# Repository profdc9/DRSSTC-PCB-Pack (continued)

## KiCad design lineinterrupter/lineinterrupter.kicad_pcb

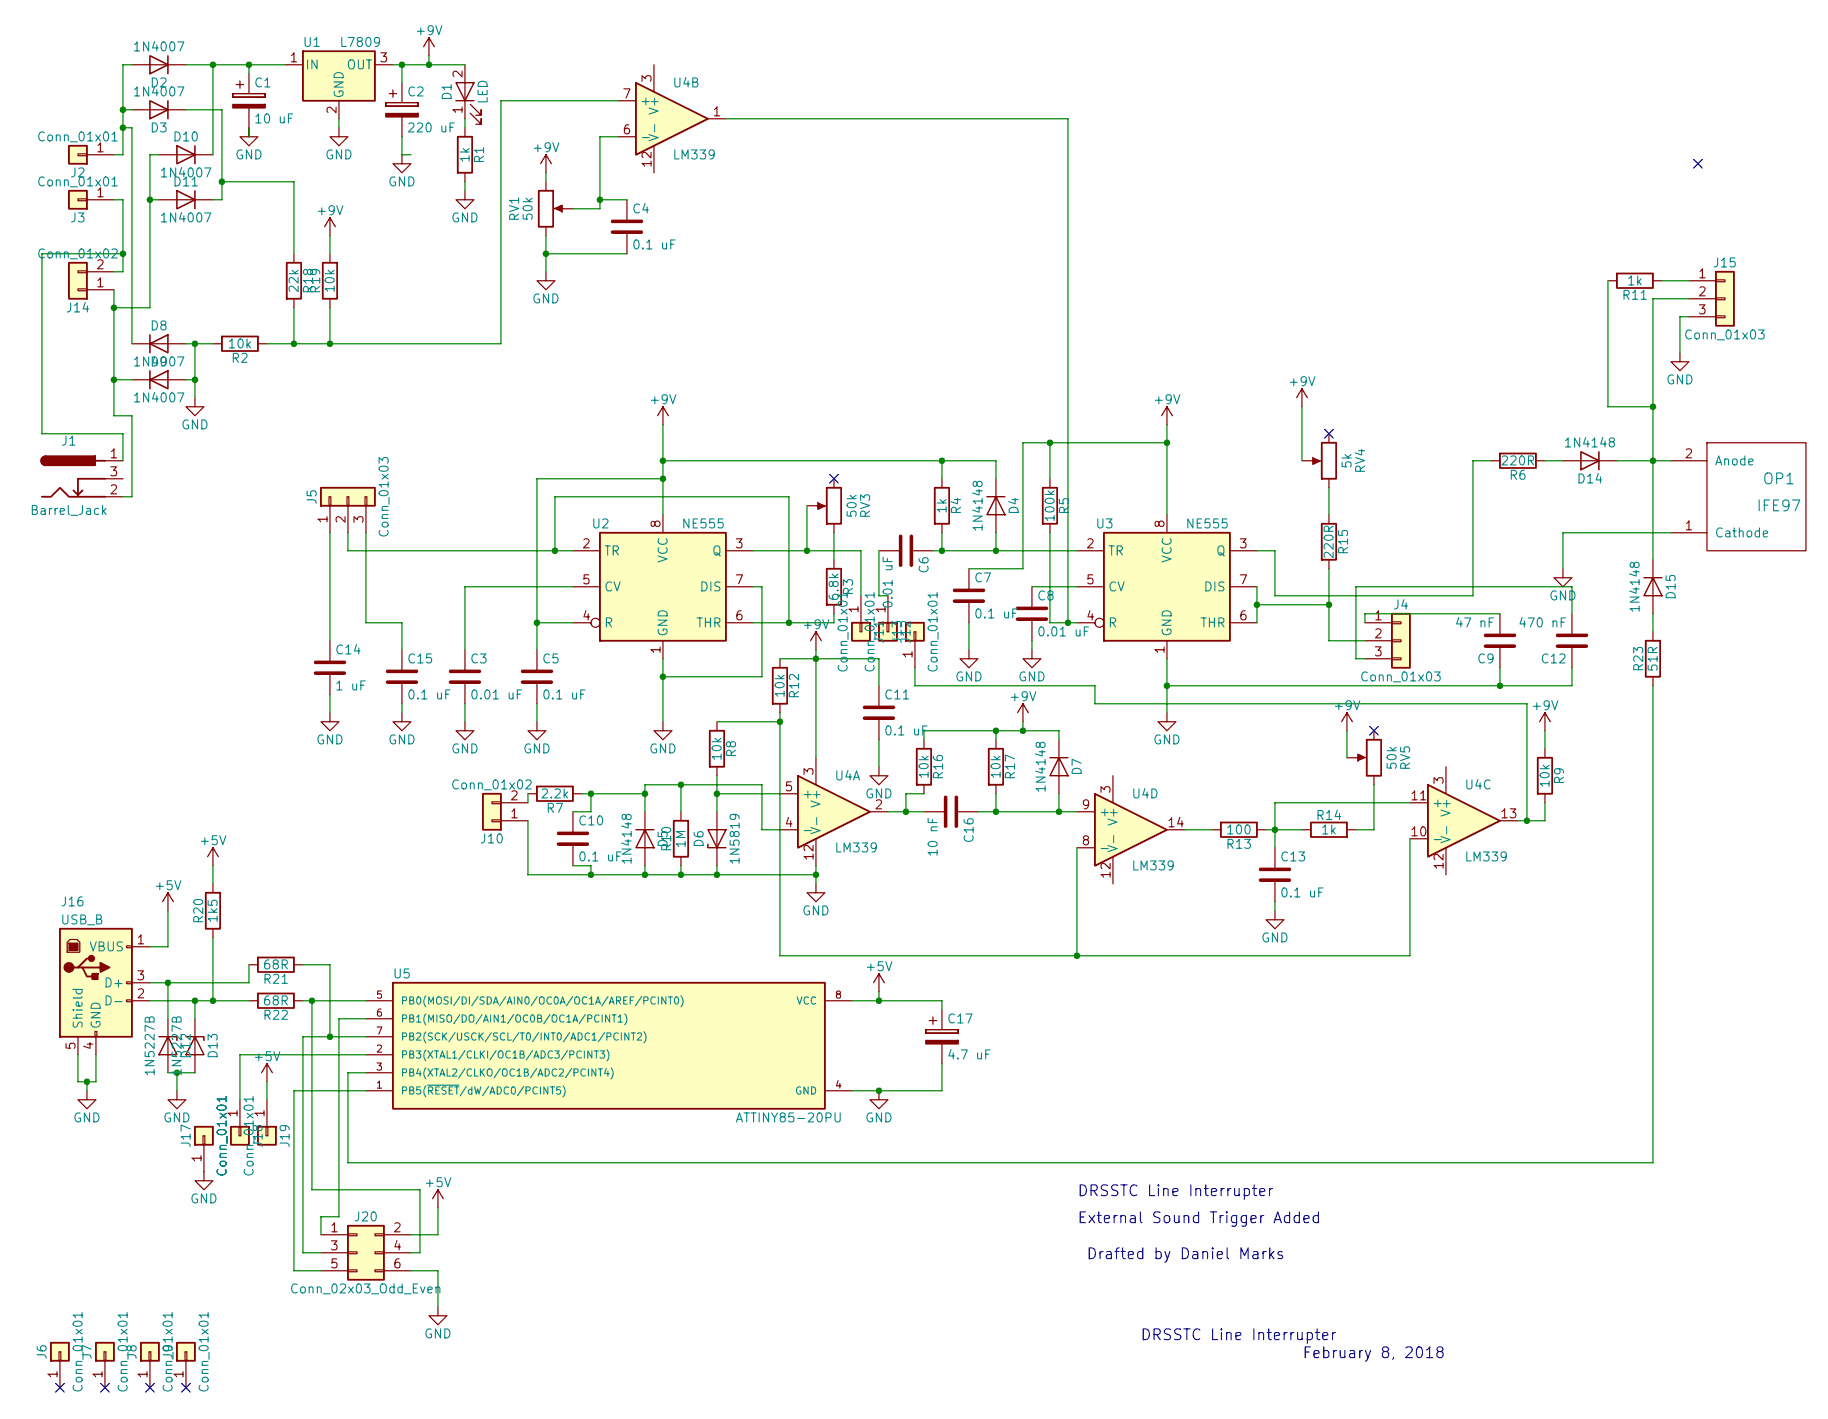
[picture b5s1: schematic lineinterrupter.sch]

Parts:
C1: 10 uF; CP_Radial_D6.3mm_P2.50mm
C2: 220 uF; CP_Radial_D6.3mm_P2.50mm
C3, C6, C8: 0.01 uF; C_Disc_D7.5mm_W4.4mm_P5.00mm
C4, C5, C7, C10, C11, C13, C15: 0.1 uF; C_Disc_D7.5mm_W4.4mm_P5.00mm
C9: 47 nF; C_Disc_D7.5mm_W4.4mm_P5.00mm
C12: 470 nF; C_Disc_D7.5mm_W4.4mm_P5.00mm
C14: 1 uF; C_Disc_D7.5mm_W4.4mm_P5.00mm
C16: 10 nF; C_Disc_D7.5mm_W4.4mm_P5.00mm
C17: 4.7 uF; CP_Radial_D6.3mm_P2.50mm
D1: LED; LED_D5.0mm
D2, D3, D8, D9, D10, D11: 1N4007; D_DO-41_SOD81_P10.16mm_Horizontal
D4, D5, D7, D14, D15: 1N4148; D_DO-41_SOD81_P7.62mm_Horizontal
D6: 1N5819; D_DO-41_SOD81_P7.62mm_Horizontal
D12, D13: 1N5227B; D_DO-41_SOD81_P10.16mm_Horizontal
J1: Barrel_Jack; BARREL_JACK
J2, J3, J6, J7, J8, J9, J11, J12, J13, J17, J18, J19: Conn_01x01; 1pin
J4, J5: Conn_01x03; Pin_Header_Straight_1x03_Pitch2.54mm
J10, J14: Conn_01x02; TerminalBlock_bornier-2_P5.08mm
J15: Conn_01x03; TerminalBlock_bornier-3_P5.08mm
J16: USB_B
J20: Conn_02x03_Odd_Even; Pin_Header_Straight_2x03_Pitch2.54mm
OP1: IFE97
R1, R4, R11, R14: 1k; R_Axial_DIN0309_L9.0mm_D3.2mm_P12.70mm_Horizontal
R2, R8, R9, R12, R16, R17, R19: 10k; R_Axial_DIN0309_L9.0mm_D3.2mm_P12.70mm_Horizontal
R3: 6.8k; R_Axial_DIN0309_L9.0mm_D3.2mm_P12.70mm_Horizontal
R5: 100k; R_Axial_DIN0309_L9.0mm_D3.2mm_P12.70mm_Horizontal
R6, R15: 220R; R_Axial_DIN0309_L9.0mm_D3.2mm_P12.70mm_Horizontal
R7: 2.2k; R_Axial_DIN0309_L9.0mm_D3.2mm_P12.70mm_Horizontal
R10: 1M; R_Axial_DIN0309_L9.0mm_D3.2mm_P12.70mm_Horizontal
R13: 100; R_Axial_DIN0309_L9.0mm_D3.2mm_P12.70mm_Horizontal
R18: 22k; R_Axial_DIN0309_L9.0mm_D3.2mm_P12.70mm_Horizontal
R20: 1k5; R_Axial_DIN0309_L9.0mm_D3.2mm_P12.70mm_Horizontal
R21, R22: 68R; R_Axial_DIN0309_L9.0mm_D3.2mm_P12.70mm_Horizontal
R23: 51R; R_Axial_DIN0309_L9.0mm_D3.2mm_P12.70mm_Horizontal
RV1, RV3, RV5: 50k; Potentiometer_WirePads
RV4: 5k; Potentiometer_WirePads
U1: L7809; TO-220-3_Vertical
U2, U3: NE555; DIP-8_W7.62mm_Socket
U4: LM339; DIP-14_W7.62mm_Socket
U5: ATTINY85-20PU; DIP-8_W7.62mm_Socket

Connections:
+5V: C17.1, J16.1 (VBUS), J19.1, J20.2, R20.2, U5.8 (VCC)
+9V: C2.1, C5.1, C7.1, C11.1, D1.2 (A), D4.1 (K), D7.1 (K), R4.1, R5.1, R9.1, R12.1, R16.1, R17.1, R19.2, RV1.1, RV4.2, RV5.2, U1.3 (OUT), U2.4 (R), U2.8 (VCC), U3.8 (VCC), U4.3 (V+)
GND: C1.2, C2.2, C3.2, C4.2, C5.2, C7.2, C8.2, C9.1, C10.2, C11.2, C12.1, C13.2, C14.2, C15.2, C17.2, D5.2 (A), D6.1 (K), D8.2 (A), D9.2 (A), D12.2 (A), D13.2 (A), J10.1, J15.3, J16.4 (GND), J16.5 (Shield), J17.1, J20.6, OP1.1 (Cathode), R1.2, R2.2, R10.1, RV1.3, U1.2 (GND), U2.1 (GND), U2.7 (DIS), U3.1 (GND), U4.12 (V-), U5.4 (GND)
unnamed: C1.1, D2.1 (K), D10.1 (K), U1.1 (IN)
unnamed: C3.1, U2.5 (CV)
unnamed: C4.1, RV1.2, U4.6 (-)
unnamed: C6.1, D4.2 (A), R4.2, U3.2 (TR)
unnamed: C6.2, J12.1
unnamed: C8.1, U3.5 (CV)
unnamed: C9.2, J4.1
unnamed: C10.1, D5.1 (K), R7.1, R10.2, U4.4 (-)
unnamed: C12.2, J4.3
unnamed: C13.1, R13.1, R14.1, U4.11 (+)
unnamed: C14.1, J5.1
unnamed: C15.1, J5.3
unnamed: C16.1, D7.2 (A), R17.2, U4.9 (+)
unnamed: C16.2, R16.2, U4.2
unnamed: D1.1 (K), R1.1
unnamed: D2.2 (A), D3.2 (A), D8.1 (K), J2.1
unnamed: D6.2 (A), R8.2, U4.5 (+)
unnamed: D9.1 (K), D10.2 (A), D11.2 (A), J1.2, J14.1
unnamed: D3.1 (K), D11.1 (K), R18.1
unnamed: D12.1 (K), J16.3 (D+), R21.2
unnamed: D13.1 (K), J16.2 (D-), R20.1, R22.2
unnamed: D14.1 (K), D15.1 (K), J15.2, OP1.2 (Anode), R11.2
unnamed: D14.2 (A), R6.1
unnamed: D15.2 (A), R23.2
unnamed: J1.1, J3.1, J14.2
unnamed: J4.2, R15.2, U3.6 (THR), U3.7 (DIS)
unnamed: J5.2, R3.2, U2.2 (TR), U2.6 (THR)
unnamed: J10.2, R7.2
unnamed: J11.1, RV3.2, U2.3 (Q)
unnamed: J13.1, R9.2, U4.13
unnamed: J15.1, R11.1
unnamed: J18.1, U5.2 (PB3(XTAL1/CLKI/OC1B/ADC3/PCINT3))
unnamed: J20.1, U5.6 (PB1(MISO/DO/AIN1/OC0B/OC1A/PCINT1))
unnamed: J20.3, R21.1, U5.7 (PB2(SCK/USCK/SCL/T0/INT0/ADC1/PCINT2))
unnamed: J20.4, R22.1, U5.5 (PB0(MOSI/DI/SDA/AIN0/OC0A/OC1A/AREF/PCI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)
unnamed: J20.5, U5.1 (PB5(~RESET~/dW/ADC0/PCINT5))
unnamed: R3.1, RV3.1
unnamed: R5.2, U3.4 (R), U4.1
unnamed: R6.2, U3.3 (Q)
unnamed: R8.1, R12.2, U4.8 (-), U4.10 (-)
unnamed: R13.2, U4.14
unnamed: R14.2, RV5.3
unnamed: R15.1, RV4.1
unnamed: R2.1, R18.2, R19.1, U4.7 (+)
unnamed: R23.1, U5.3 (PB4(XTAL2/CLKO/OC1B/ADC2/PCINT4))

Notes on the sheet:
DRSSTC Line Interrupter
DRSSTC Line Interrupter
External Sound Trigger Added
February 8, 2018
Drafted by Daniel Marks

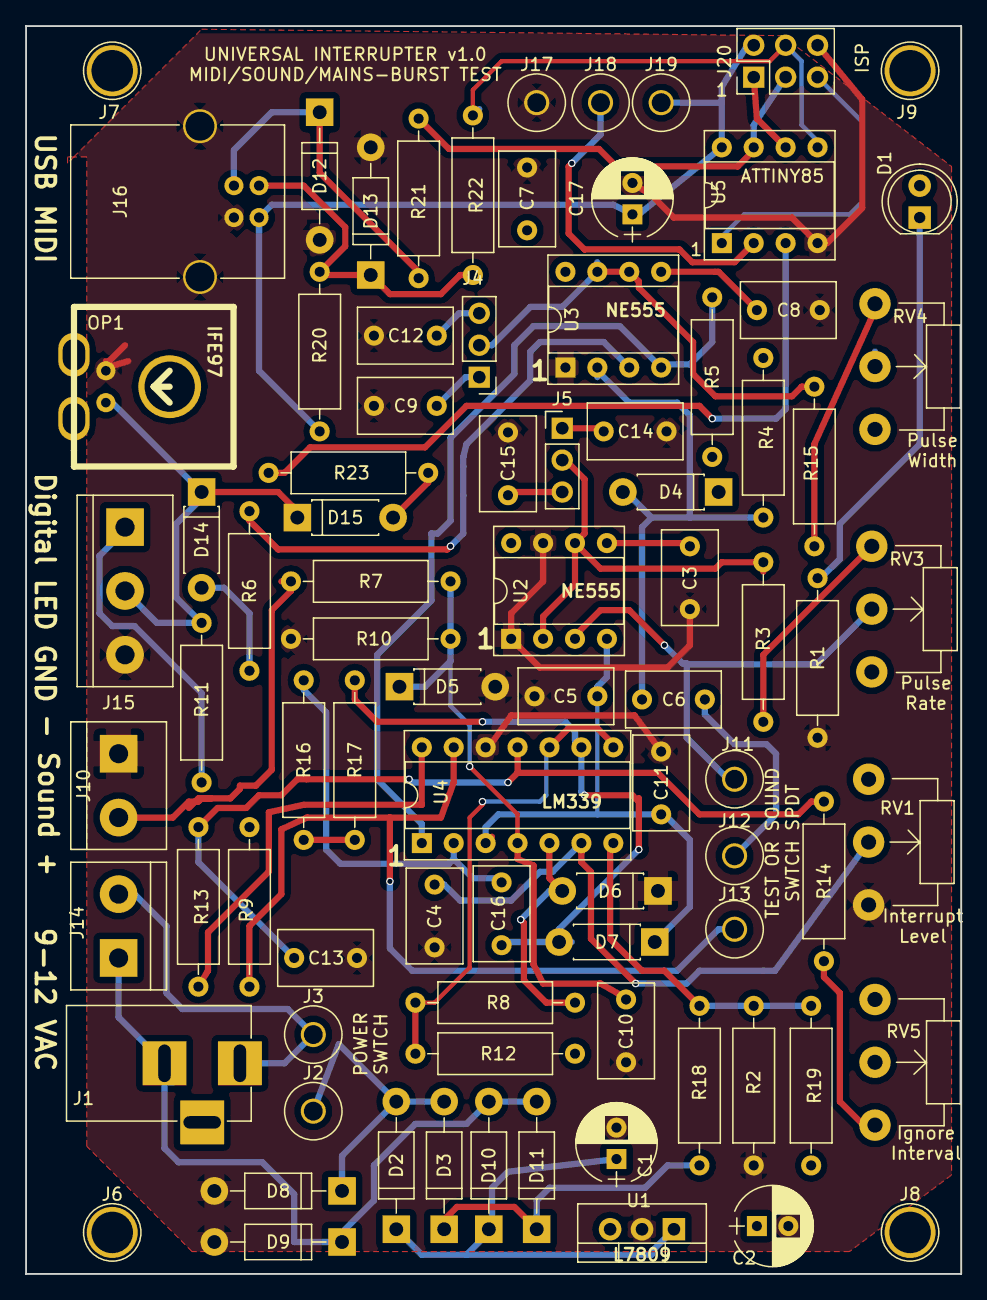
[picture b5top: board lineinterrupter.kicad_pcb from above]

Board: 2 copper layers, 74.4 x 99.3 mm, 85 parts (0 on the bottom side), 48 nets.

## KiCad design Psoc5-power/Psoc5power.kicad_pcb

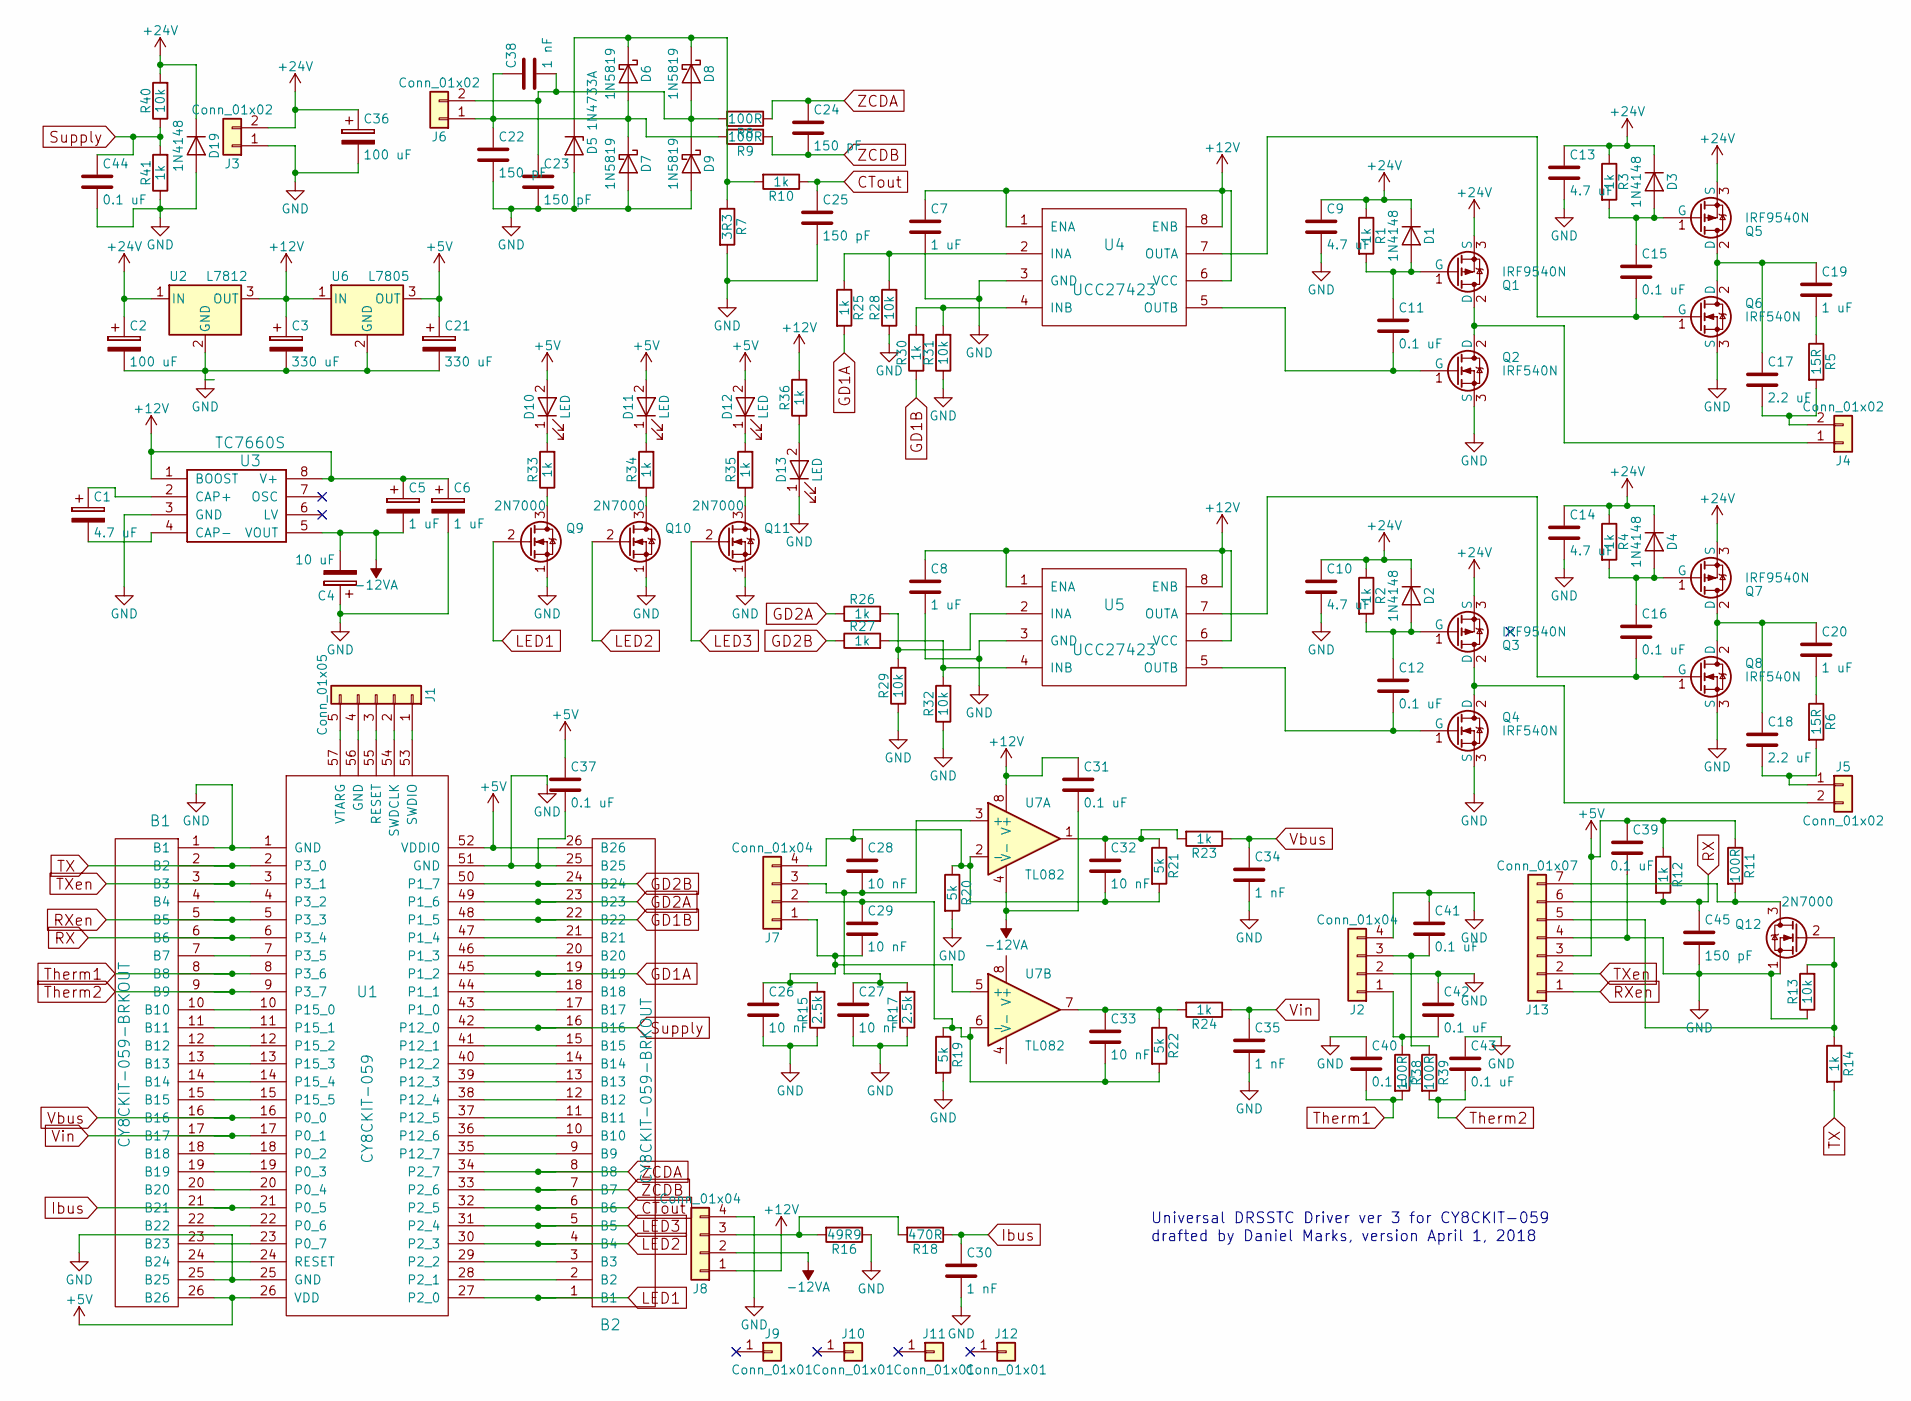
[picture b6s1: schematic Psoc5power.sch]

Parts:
B1, B2: CY8CKIT-059-BRKOUT
C1: 4.7 uF; CP_Radial_D6.3mm_P2.50mm
C2, C36: 100 uF; CP_Radial_D10.0mm_P5.00mm
C3, C21: 330 uF; CP_Radial_D10.0mm_P5.00mm
C4: 10 uF; CP_Radial_D6.3mm_P2.50mm
C5, C6: 1 uF; CP_Radial_D5.0mm_P2.50mm
C7, C8: 1 uF; C_Disc_D5.0mm_W2.5mm_P5.00mm
C9, C10, C13, C14: 4.7 uF; C_Disc_D7.5mm_W2.5mm_P5.00mm
C11, C12, C15, C16, C31, C37, C39, C40, C41, C42, C43, C44: 0.1 uF; C_Disc_D5.0mm_W2.5mm_P5.00mm
C17, C18: 2.2 uF; C_Disc_D7.5mm_W2.5mm_P5.00mm
C19, C20: 1 uF; C_Disc_D7.5mm_W2.5mm_P5.00mm
C22, C23, C24, C25, C45: 150 pF; C_Disc_D5.0mm_W2.5mm_P5.00mm
C26, C27, C32, C33: 10 nF; C_Disc_D5.0mm_W2.5mm_P5.00mm
C28, C29: 10 nF; C_Disc_D6.0mm_W2.5mm_P5.00mm
C30, C34, C35, C38: 1 nF; C_Disc_D5.0mm_W2.5mm_P5.00mm
D1, D2, D3, D4: 1N4148; D_DO-41_SOD81_P10.16mm_Horizontal
D5: 1N4733A; D_DO-41_SOD81_P10.16mm_Horizontal
D6, D7, D8, D9: 1N5819; D_DO-41_SOD81_P10.16mm_Horizontal
D10, D11, D12, D13: LED; LED_D3.0mm
D19: 1N4148; D_DO-35_SOD27_P7.62mm_Horizontal
J1: Conn_01x05; Pin_Header_Straight_1x05_Pitch2.54mm
J2, J7, J8: Conn_01x04; Molex_KK-6410-04_04x2.54mm_Straight
J3, J4, J5, J6: Conn_01x02; TerminalBlock_bornier-2_P5.08mm
J9, J10, J11, J12: Conn_01x01; 1pin
J13: Conn_01x07; Molex_KK-6410-07_07x2.54mm_Straight
Q1, Q3, Q5, Q7: IRF9540N; TO-220-3_Vertical
Q2, Q4, Q6, Q8: IRF540N; TO-220-3_Vertical
Q9, Q10, Q11, Q12: 2N7000; TO-92_Molded_Narrow
R1, R2, R3, R4, R10, R12, R14, R23, R24, R25, R26, R27, R30, R33, R34, R35, R36, R41: 1k; R_Axial_DIN0207_L6.3mm_D2.5mm_P7.62mm_Horizontal
R5, R6: 15R; R_Axial_DIN0414_L11.9mm_D4.5mm_P15.24mm_Horizontal
R7: 3R3; R_Axial_DIN0309_L9.0mm_D3.2mm_P12.70mm_Horizontal
R8, R9: 100R; R_Axial_DIN0309_L9.0mm_D3.2mm_P12.70mm_Horizontal
R11, R38, R39: 100R; R_Axial_DIN0207_L6.3mm_D2.5mm_P7.62mm_Horizontal
R13, R28, R29, R31, R32, R40: 10k; R_Axial_DIN0207_L6.3mm_D2.5mm_P7.62mm_Horizontal
R15, R17: 2.5k; R_Axial_DIN0207_L6.3mm_D2.5mm_P7.62mm_Horizontal
R16: 49R9; R_Axial_DIN0207_L6.3mm_D2.5mm_P7.62mm_Horizontal
R18: 470R; R_Axial_DIN0207_L6.3mm_D2.5mm_P7.62mm_Horizontal
R19, R20, R21, R22: 5k; R_Axial_DIN0207_L6.3mm_D2.5mm_P7.62mm_Horizontal
U1: CY8CKIT-059
U2: L7812; TO-220-3_Vertical
U3: TC7660S; DIP-8_W7.62mm_Socket
U4, U5: UCC27423; DIP-8_W7.62mm_Socket
U6: L7805; TO-220-3_Vertical
U7: TL082; DIP-8_W7.62mm_Socket

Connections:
+5V: B1.26 (B26), B2.26 (B26), C21.1, C37.1, C39.1, D10.2 (A), D11.2 (A), D12.2 (A), J13.3, R11.1, R12.1, U1.26 (VDD), U1.52 (VDDIO), U6.3 (OUT)
+24V: C2.1, C9.1, C10.1, C13.1, C14.1, C36.1, D1.1 (K), D2.1 (K), D3.1 (K), D4.1 (K), D19.1 (K), J3.2, Q1.3 (S), Q3.3 (S), Q5.3 (S), Q7.3 (S), R1.1, R2.1, R3.1, R4.1, R40.2, U2.1 (IN)
-12VA: C4.2, C5.2, C31.2, J8.2, U3.5 (VOUT), U7.4 (V-)
CTout: B2.6 (B6), C25.1, R10.1, U1.32 (P2_5)
GD1A: B2.19 (B19), R25.2, U1.45 (P1_2)
GD1B: B2.22 (B22), R30.1, U1.48 (P1_5)
GD2A: B2.23 (B23), R26.1, U1.49 (P1_6)
GD2B: B2.24 (B24), R27.1, U1.50 (P1_7)
GND: B1.1 (B1), B1.25 (B25), B2.25 (B25), C2.2, C3.2, C4.1, C6.2, C7.2, C8.2, C9.2, C10.2, C13.2, C14.2, C21.2, C22.2, C23.2, C25.2, C26.2, C27.2, C30.2, C34.2, C35.2, C36.2, C37.2, C39.2, C40.1, C41.1, C42.1, C43.1, C44.2, C45.2, D5.2 (A), D7.2 (A), D9.2 (A), D13.1 (K), D19.2 (A), J2.2, J2.4, J3.1, J8.4, J13.4, Q2.3 (S), Q4.3 (S), Q6.3 (S), Q8.3 (S), Q9.1 (S), Q10.1 (S), Q11.1 (S), Q12.1 (S), R7.2, R13.1, R15.1, R16.1, R17.1, R19.2, R20.2, R28.1, R29.1, R31.1, R32.1, R41.1, U1.1 (GND), U1.25 (GND), U1.51 (GND), U2.2 (GND), U3.3 (GND), U4.3 (GND), U5.3 (GND), U6.2 (GND)
Ibus: B1.21 (B21), C30.1, R18.1, U1.21 (P0_5)
LED1: B2.1 (B1), Q9.2 (G), U1.27 (P2_0)
LED2: B2.4 (B4), Q10.2 (G), U1.30 (P2_3)
LED3: B2.5 (B5), Q11.2 (G), U1.31 (P2_4)
unnamed: B1.4 (B4), U1.4 (P3_2)
unnamed: B1.7 (B7), U1.7 (P3_5)
unnamed: B1.10 (B10), U1.10 (P15_0)
unnamed: B1.11 (B11), U1.11 (P15_1)
unnamed: B1.12 (B12), U1.12 (P15_2)
unnamed: B1.13 (B13), U1.13 (P15_3)
unnamed: B1.14 (B14), U1.14 (P15_4)
unnamed: B1.15 (B15), U1.15 (P15_5)
unnamed: B1.18 (B18), U1.18 (P0_2)
unnamed: B1.19 (B19), U1.19 (P0_3)
unnamed: B1.20 (B20), U1.20 (P0_4)
unnamed: B1.22 (B22), U1.22 (P0_6)
unnamed: B1.23 (B23), U1.23 (P0_7)
unnamed: B1.24 (B24), U1.24 (RESET)
unnamed: B2.2 (B2), U1.28 (P2_1)
unnamed: B2.3 (B3), U1.29 (P2_2)
unnamed: B2.9 (B9), U1.35 (P12_7)
unnamed: B2.10 (B10), U1.36 (P12_6)
unnamed: B2.11 (B11), U1.37 (P12_5)
unnamed: B2.12 (B12), U1.38 (P12_4)
unnamed: B2.13 (B13), U1.39 (P12_3)
unnamed: B2.14 (B14), U1.40 (P12_2)
unnamed: B2.15 (B15), U1.41 (P12_1)
unnamed: B2.17 (B17), U1.43 (P1_0)
unnamed: B2.18 (B18), U1.44 (P1_1)
unnamed: B2.20 (B20), U1.46 (P1_3)
unnamed: B2.21 (B21), U1.47 (P1_4)
unnamed: C1.1, U3.2 (CAP+)
unnamed: C1.2, U3.4 (CAP-)
unnamed: C11.1, D1.2 (A), Q1.1 (G), R1.2
unnamed: C11.2, Q2.1 (G), U4.5 (OUTB)
unnamed: C12.1, D2.2 (A), Q3.1 (G), R2.2
unnamed: C12.2, Q4.1 (G), U5.5 (OUTB)
unnamed: C15.1, D3.2 (A), Q5.1 (G), R3.2
unnamed: C15.2, Q6.1 (G), U4.7 (OUTA)
unnamed: C16.1, D4.2 (A), Q7.1 (G), R4.2
unnamed: C16.2, Q8.1 (G), U5.7 (OUTA)
unnamed: C17.1, C19.1, Q5.2 (D), Q6.2 (D)
unnamed: C17.2, J4.2, R5.2
unnamed: C18.1, C20.1, Q7.2 (D), Q8.2 (D)
unnamed: C18.2, J5.1, R6.2
unnamed: C19.2, R5.1
unnamed: C20.2, R6.1
unnamed: C22.1, C38.1, D6.2 (A), D7.1 (K), J6.1, R9.2
unnamed: C23.1, C38.2, D8.2 (A), D9.1 (K), J6.2, R8.2
unnamed: C26.1, C29.2, J7.1, R15.2, U7.5 (+)
unnamed: C27.1, C28.2, J7.3, R17.2, U7.3 (+)
unnamed: C28.1, C32.2, J7.4, R20.1, R21.2, U7.2 (-)
unnamed: C29.1, C33.2, J7.2, R19.1, R22.2, U7.6 (-)
unnamed: C32.1, R21.1, R23.2, U7.1
unnamed: C33.1, R22.1, R24.2, U7.7
unnamed: C41.2, J2.3, R39.1
unnamed: C42.2, J2.1, R38.1
unnamed: D5.1 (K), D6.1 (K), D8.1 (K), R7.1, R10.2
unnamed: D10.1 (K), R33.2
unnamed: D11.1 (K), R34.2
unnamed: D12.1 (K), R35.2
unnamed: D13.2 (A), R36.1
unnamed: J1.1, U1.53 (SWDIO)
unnamed: J1.2, U1.54 (SWDCLK)
unnamed: J1.3, U1.55 (RESET)
unnamed: J1.4, U1.56 (GND)
unnamed: J1.5, U1.57 (VTARG)
unnamed: J4.1, Q1.2 (D), Q2.2 (D)
unnamed: J5.2, Q3.2 (D), Q4.2 (D)
unnamed: J13.5, Q12.2 (G), R13.2, R14.1
unnamed: J13.7, Q12.3 (D), R11.2
unnamed: Q9.3 (D), R33.1
unnamed: Q10.3 (D), R34.1
unnamed: Q11.3 (D), R35.1
unnamed: R25.1, R28.2, U4.2 (INA)
unnamed: R26.2, R29.2, U5.2 (INA)
unnamed: R27.2, R32.2, U5.4 (INB)
unnamed: R30.2, R31.2, U4.4 (INB)
RX: B1.6 (B6), C45.1, J13.6, R12.2, U1.6 (P3_4)
RXen: B1.5 (B5), J13.1, U1.5 (P3_3)
Supply: B2.16 (B16), C44.1, R40.1, R41.2, U1.42 (P12_0)
TX: B1.2 (B2), R14.2, U1.2 (P3_0)
TXen: B1.3 (B3), J13.2, U1.3 (P3_1)
Therm1: B1.8 (B8), C40.2, R38.2, U1.8 (P3_6)
Therm2: B1.9 (B9), C43.2, R39.2, U1.9 (P3_7)
Vbus: B1.16 (B16), C34.1, R23.1, U1.16 (P0_0)
Vin: B1.17 (B17), C35.1, R24.1, U1.17 (P0_1)
ZCDA: B2.8 (B8), C24.1, R8.1, U1.34 (P2_7)
ZCDB: B2.7 (B7), C24.2, R9.1, U1.33 (P2_6)

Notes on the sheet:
Universal DRSSTC Driver ver 3 for CY8CKIT-059
drafted by Daniel Marks, version April 1, 2018

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
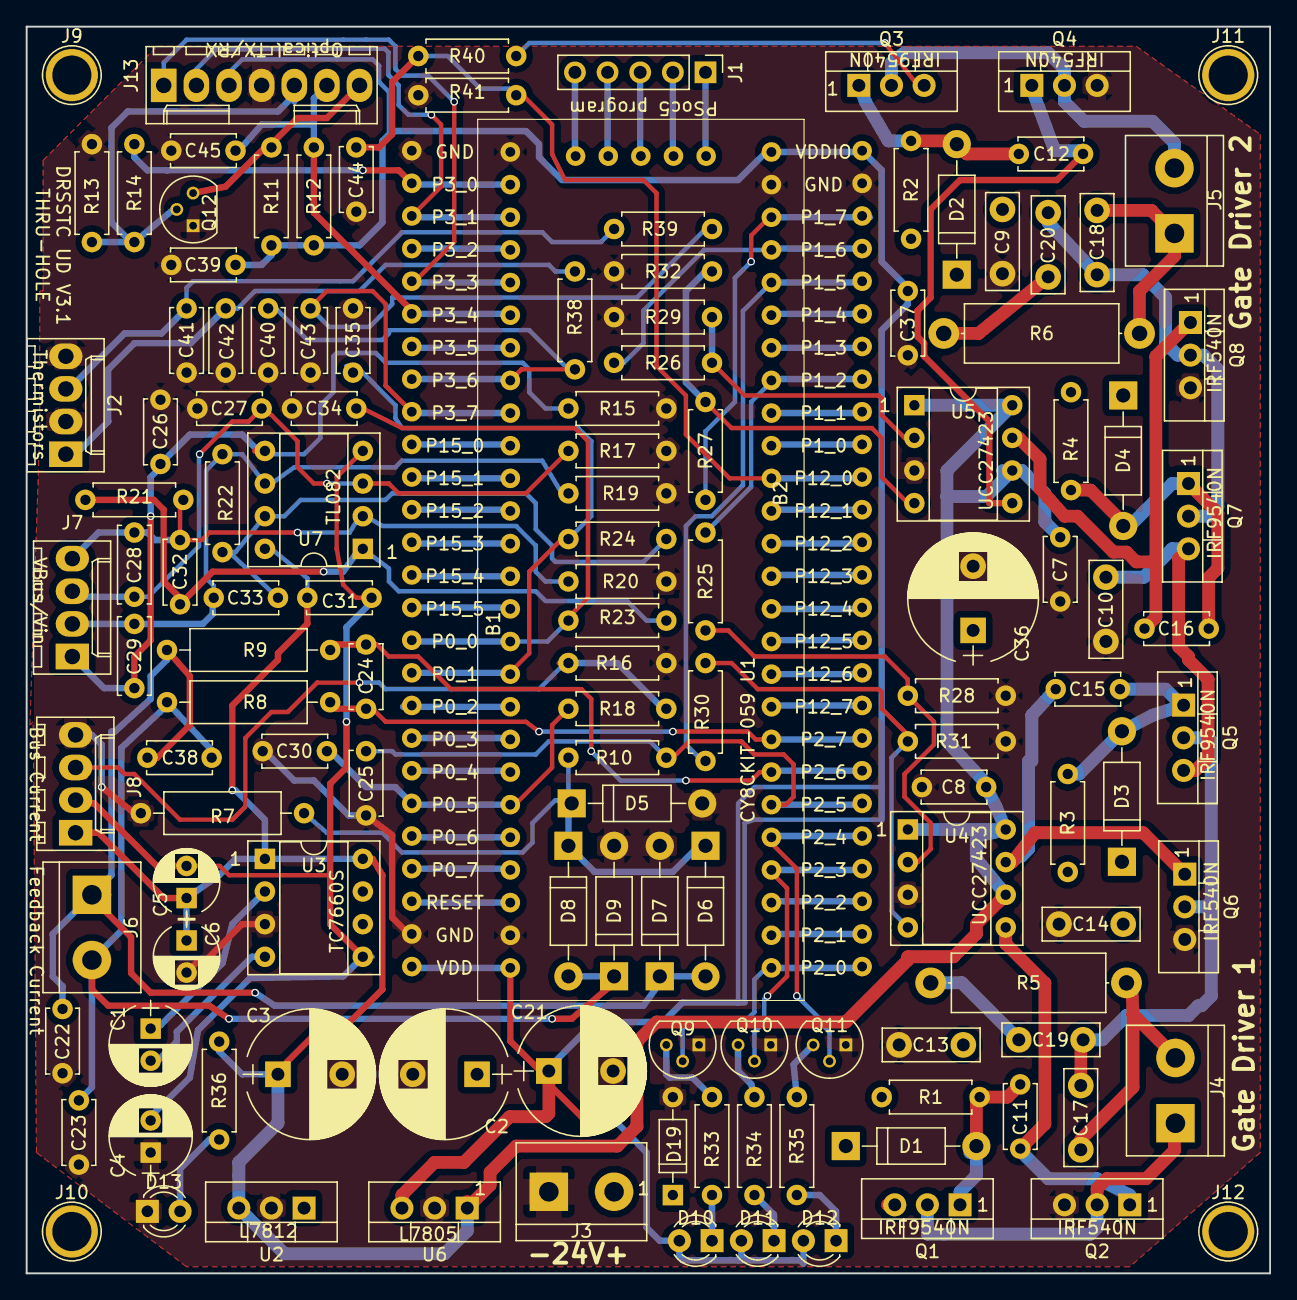
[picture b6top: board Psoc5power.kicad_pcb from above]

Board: 2 copper layers, 96.8 x 97.0 mm, 133 parts (0 on the bottom side), 100 nets.

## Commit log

2019-03-29 Fixed long dead time problem on half-bridge-sstc
2019-07-12 Cleaned up labels and pads on half/full bridge boards
2020-11-19 Added optional frequency halving to ensure 50% duty cycle
2023-02-14 kicad update 6.0.11
2023-02-14 redrawn schematic
2023-02-14 gitignore update
2023-02-14 html BOM
2023-05-03 minor changes
